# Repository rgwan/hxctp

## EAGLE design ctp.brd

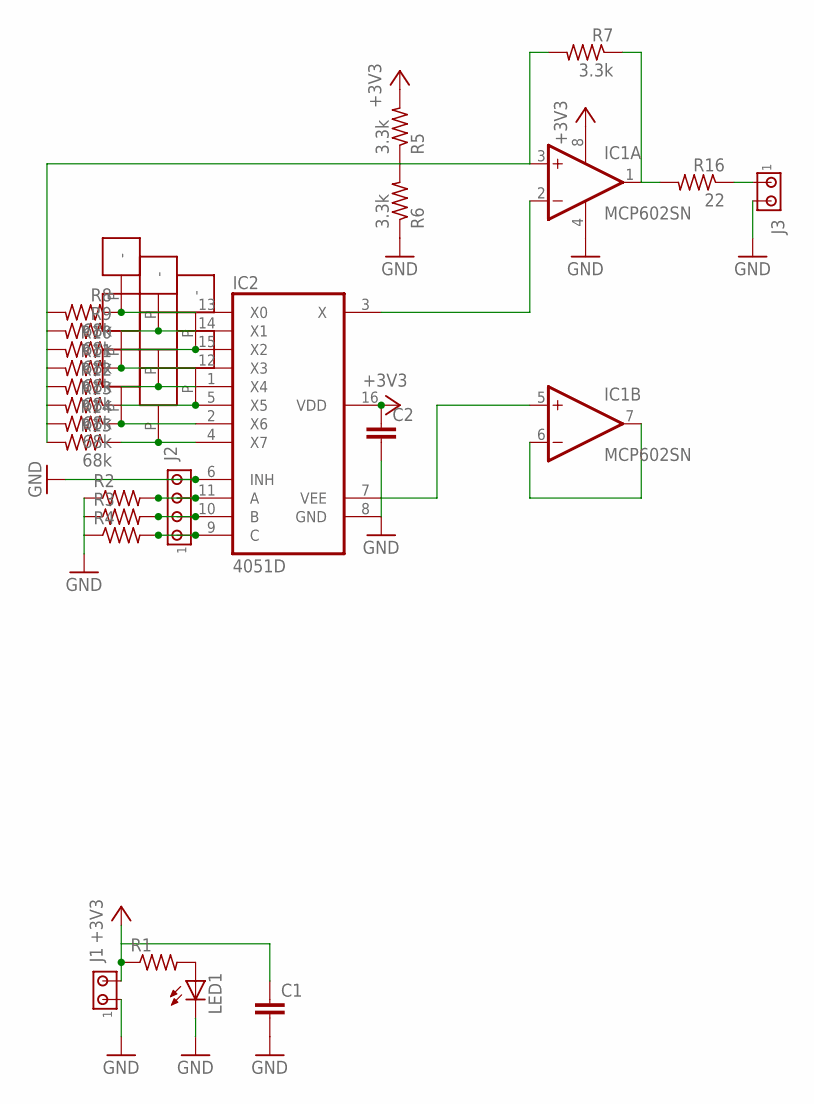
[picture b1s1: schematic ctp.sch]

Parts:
C1, C2: C-EUC0805; C0805
IC1: MCP602SN; SO08
IC2: 4051D; SO16
J1, J3: MTA02-100; 10X02MTA
J2: MTA04-100; 10X04MTA
LED1: LEDCHIP-LED0805; CHIP-LED0805
R1, R2, R3, R4: R-US_M0805; M0805
R5, R6, R7: 3.3k; M0805
R8, R9, R10, R11, R12, R13, R14, R15: 68k; M0805
R16: 22; M0805
U$1, U$2, U$3, U$4, U$5, U$6, U$7, U$8: BUTTON; CTP1

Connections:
+3V3: C1.1, C2.1, IC1.8 (V+), IC2.16 (VDD), J1.2, R1.1, R5.2
GND: C1.2, C2.2, IC1.4 (V-), IC1.5 (+IN), IC2.6 (INH), IC2.7 (VEE), IC2.8 (GND), J1.1, J2.4, J3.2, LED1.C, R2.1, R3.1, R4.1, R6.1
unnamed: LED1.A, R1.2
unnamed: IC2.9 (C), J2.1, R4.2
unnamed: IC2.11 (A), J2.3, R2.2
unnamed: IC2.10 (B), J2.2, R3.2
unnamed: IC1.3 (+IN), R5.1, R6.2, R7.2, R8.2, R9.2, R10.2, R11.2, R12.2, R13.2, R14.2, R15.2
unnamed: IC1.6 (-IN), IC1.7 (OUT)
unnamed: IC1.1 (OUT), R7.1, R16.2
unnamed: IC1.2 (-IN), IC2.3 (X)
unnamed: IC2.13 (X0), R8.1, U$1.P
unnamed: IC2.14 (X1), R9.1, U$2.P
unnamed: IC2.15 (X2), R10.1, U$3.P
unnamed: IC2.12 (X3), R11.1, U$4.P
unnamed: IC2.1 (X4), R12.1, U$5.P
unnamed: IC2.5 (X5), R13.1, U$6.P
unnamed: IC2.2 (X6), R14.1, U$7.P
unnamed: IC2.4 (X7), R15.1, U$8.P
unnamed: J3.1, R16.1

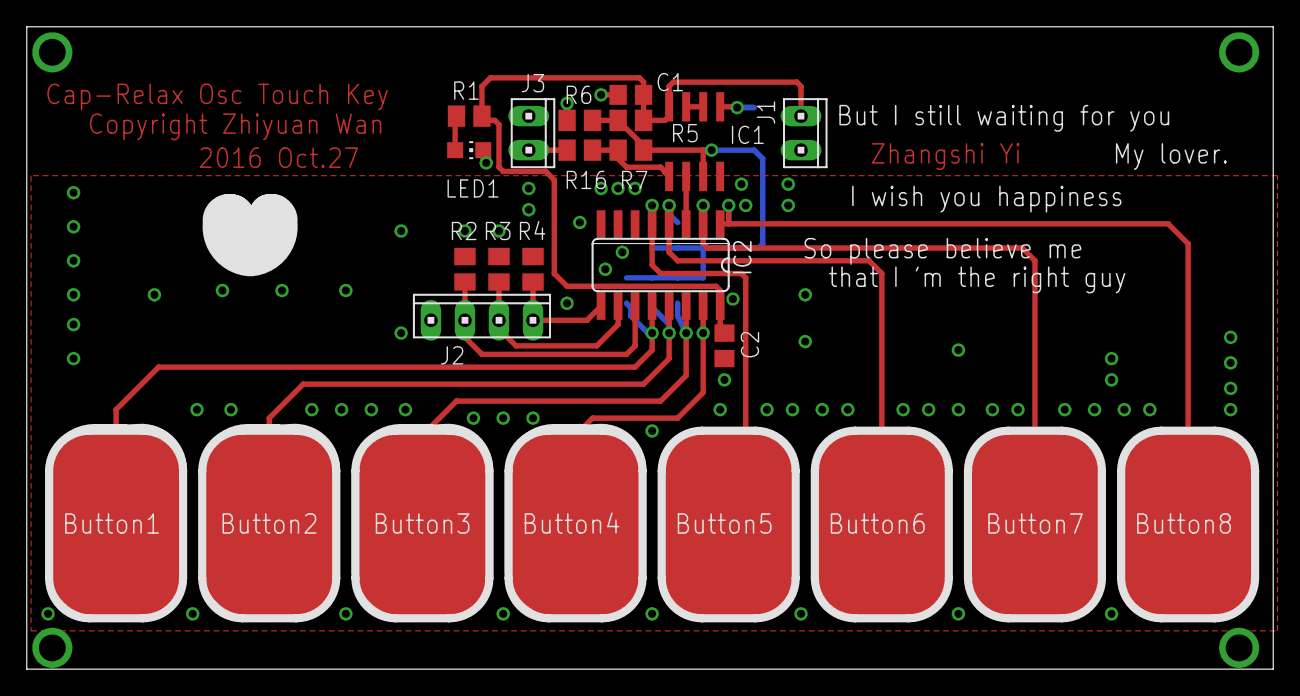
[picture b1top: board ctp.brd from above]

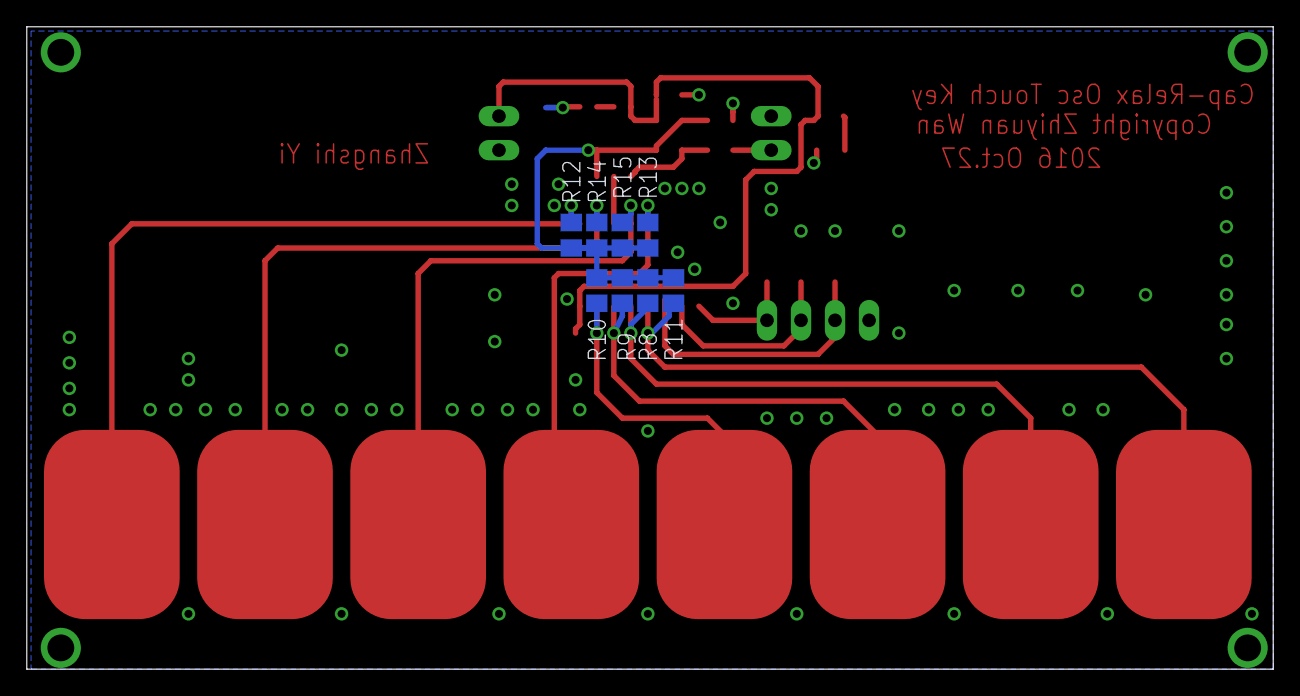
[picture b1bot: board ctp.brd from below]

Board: 2 copper layers, 93.0 x 47.9 mm, 32 parts (8 on the bottom side), 19 nets.

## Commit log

2016-12-12 Schematic

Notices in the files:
ctp.brd:
Copyright Zhiyuan Wan
